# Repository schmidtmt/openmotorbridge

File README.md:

# OpenMotorBridge (v10.0) - Universal Motorcycle Intercom & Telemetry Bridge

<p align="center">
  
  &nbsp;&nbsp;&nbsp;&nbsp;&nbsp;&nbsp;&nbsp;&nbsp;
  
</p>

<p align="center">

</p>

**OpenMotorBridge (OMB)** is an open-source, cross-vendor communication and telemetry bridge for motorcycles. It seamlessly interconnects proprietary wireless intercom systems (**Sena Mesh 3.0** and **Cardo DMC Gen2**) with an open **2.4 GHz / 868 MHz OpenMotorMesh (OMM)**, high-precision **GNSS Tour Logging (Automotive Dead Reckoning)**, and a **wireless WebBLE PWA cockpit dashboard**.

---

## 📚 Technical Documentation

The comprehensive technical specification is split into 18 logically organized chapters:

1. [**01 - System Architecture & Satellite Topology**](docs/en/01_system_architecture.md)  
   *The 5 standardized functional nodes, de-sensing philosophy, RF diversity, whitepaper engineering decisions, and cockpit integration.*

2. [**02 - Intercom Matrix, Hardware Profiles & Routing**](docs/en/02_intercom_matrix_profiles.md)  
   *The 5 OEM adapter classes A-E, LittleFS profile engine, zero-latency PTT (< 1.8 ms), and audio cross-matrix.*

3. [**03 - Audio DSP, Acoustics & Knowles MEMS Wind Tracking**](docs/en/03_audio_dsp_acoustics.md)  
   *1500V Bourns isolation, ES8388 Codec, Knowles MEMS acoustic wind sampling, and Raised-Cosine Ducking.*

4. [**04 - Mesh Network, LoRa & GNSS Navigation**](docs/en/04_mesh_lora_navigation.md)  
   *OpenMotorMesh (OMM), Dynamic Leader Election (DLE), 868 MHz LoRa fallback, and 10 Hz Multi-GNSS.*

5. [**05 - Power Management, UPS Battery & Power Gate**](docs/en/05_power_management_ups.md)  
   *LM5164-Q1 72V buck, BQ24075 UPS, TPS4H160-Q1 Quad Smart Switch, Front Node TPS54302 / SW3526 30W PD & 1-click CarPlay hard reboot.*

6. [**06 - Telemetry Blackbox, SDIO Ringbuffer & WebDAV Sync**](docs/en/06_telemetry_blackbox_webdav.md)  
   *4-bit high-speed SDIO, GDPR/court-compliant ringbuffer, ECDSA SHA-256, and automated private cloud sync.*

7. [**07 - Hardware Architecture & Board Pinouts (All 10 PCBAs)**](docs/en/07_pcba_hardware_pinouts.md)  
   *All 10 active circuit boards: layer stackup, controlled impedance, net classes, functional zoning, and pinout tables (`PCBA 01`, `03`, `05`, `05B`, `05C`, `05D`, `07`, `08`, `09`, `10`).*

8. [**08 - Mechanical Enclosures, CAD & Reference Mounting Kits**](docs/en/08_enclosures_mechanics_cad.md)  
   *Screwless Dual-Rail Slide-In Monocoques (Type A & B), Under-Perch Mirror Pod (`PCBA 05C`), 5-Port Glovebox Hub (`PCBA 05B`), Sensor Puck (`PCBA 05D`), Radar 2.0 Winged Housing with Garmin Bayonet, and 4-pin IP67 magnetic breakaway couplers.*

9. [**09 - Firmware Architecture, FreeRTOS & Rollback-OTA**](docs/en/09_firmware_architecture.md)  
   *Multi-core ESP32-S31 (Main) & ESP32-S31 + ESP32-E22 (Front), Pod Co-Processors (ESP32-C6), ESP-NOW low-latency protocol (< 1.8 ms), and dual-bank rollback OTA.*

10. [**10 - WebApp PWA & Dashboard Operation**](docs/en/10_webapp_pwa_dashboard.md)  
    *Zero-cloud PWA web app, Web Bluetooth API (WebBLE), vehicle dynamics HUD, Front Node controls, Support-Van / Convoy profile modes, and 4-tier GPX export.*

11. [**11 - Smart-Managed CarPlay & Android Auto Bridge Architecture (PCBA 05)**](docs/en/11_carplay_android_auto_bridge_architecture.md)  
    *Harley Skyline OS / Boom! Box integration, CP2AA protocol bridge, Virtual WHIM bypass, source-gated handlebar controls & headless dongle management.*

12. [**12 - Vehicle CAN-Bus Profiles, DBC JSON Schema & Universal Telemetry Engine**](docs/en/12_can_bus_vehicle_profiles.md)  
    *Data-driven LittleFS profiles for Harley-Davidson, BMW Motorrad, KTM, and OBD2, passive listen-only protection, and EKF tunnel dead reckoning.*

13. [**13 - Digital Simulation & Multi-Physics Master Testbench**](docs/en/13_simulation_testbench.md)  
    *9 modular Python testbenches and 10 HIL scenarios verifying SPICE, thermal, transients, RF, and acoustics.*

14. [**14 - EMC Hardening, RF Shielding & Environmental Protection**](docs/en/14_emv_rf_hardening.md)  
    *Automotive transient immunity (ISO 7637-2), 2.4 GHz vs 868 MHz isolation, IPC-CC-830B coating, and shock damping.*

15. [**15 - Bill of Materials (BOM) & SMT Manufacturing (All 10 PCBAs)**](docs/en/15_bom_manufacturing.md)  
    *Complete 10-board BOM for JLCPCB SMT production, ordering checklist, two-cable backbone harness, and COTS items.*

16. [**16 - Build Instructions, Wiring & Vehicle Installation**](docs/en/16_build_instructions_assembly.md)  
    *Step-by-step assembly guide for screwless v10 Slide-In Monocoques, 3D printing parameters (FDM vs. MJF), Front Node & Glovebox Hub mounting, Harley 4-pin magnetic side-wall pass-through, Smart-Keyfob build, and commissioning.*

17. [**17 - Automotive Standards & Technical References**](docs/en/17_standards_references.md)  
    *Index for ISO 7637-2, ISO 16750, ECE R10, RED 2014/53/EU, IEC 61672-1 Class 1, and Bluetooth SIG.*

18. [**18 - Legal Compliance, Privacy (GDPR) & Licensing**](docs/en/18_legal_compliance_dsgvo.md)  
    *Open-source licenses (GPL-3.0, CERN-OHL-S v2, CC BY-SA 4.0), GDPR compliance, and liability disclaimer.*

---

## 🛠️ Repository Layout

* **`docs/de/`**: Complete technical specifications in German.
* **`docs/en/`**: Complete technical specifications in English.
* **`firmware/main_controller/`**: ESP-IDF / C++ source code for the central main box (ESP32-S31, PCBA 01).
* **`firmware/front_node/`**: ESP-IDF / C++ source code for the Universal Front Node (ESP32-S31 + ESP32-E22, PCBA 05).
* **`firmware/smart_cartridge/`**: ESP-IDF / C++ source code for Saddlebag Pod Gateways Pod 1 & 2 (ESP32-C6, PCBA 03).
* **`firmware/radar_submcu/`**: ESP-IDF / C++ source code for Heck-Radar 2.0 Sub-MCU & Halo Wings (ESP32-C5, PCBA 08).
* **`webapp_pwa/`**: Zero-cloud offline WebBLE dashboard (HTML5, Vanilla JS, CSS3, Service Worker, i18n).
* **`hardware/`**: KiCad schematics, Gerber files, and 3D enclosure CAD models.
* **`tools/audio_testbench/`**: **Interactive Live Audio DSP Studio & Real-Time Testbench** (`python3 tools/audio_testbench/server.py` $\rightarrow$ Web Audio testbench with live mic, Spacebar PTT, speedometer & ducking).
* **`tools/simulators/`**: 9 modular Python simulation testbenches (`python3 tools/run_all_simulations.py`).

---

## 📜 Licenses

* **Hardware & PCB Layouts:** [CERN-OHL-S v2](https://ohwr.org/project/cernohl/wikis/Documents/CERN-OHL-version-2) (Strongly Reciprocal)
* **Firmware & Web Dashboard:** [GNU General Public License v3.0 (GPL-3.0)](https://www.gnu.org/licenses/gpl-3.0.html)
* **Documentation & 3D Models:** [Creative Commons Attribution-ShareAlike 4.0 International (CC BY-SA 4.0)](https://creativecommons.org/licenses/by-sa/4.0/)

---

## ⚠️ Liability Disclaimer

All information, schematics, board layouts, 3D printing files, and software published in this project are provided free of charge on an "AS IS" basis. Assembly, installation, and operation occur entirely at the user's own risk. All mentioned brand names (Harley-Davidson®, BMW®, Garmin®, Sena®, Cardo®, Apple CarPlay®) are registered trademarks of their respective owners.

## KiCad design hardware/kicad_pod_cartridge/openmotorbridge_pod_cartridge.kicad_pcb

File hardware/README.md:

# OpenMotorBridge v8.5 / v9.0 - KiCad Hardware-Baukasten (Clean All-UWB Architecture)

Dieses Verzeichnis enthält die vollständigen **KiCad 10 Schaltplan-, PCB- und Produktionsdateien** für die drahtlose **All-UWB & Pure-DC Architektur** von OpenMotorBridge.

---

## 📂 Das bereinigte 6-Platinen-Lineup

Durch den konsequenten Einsatz von Ultra-Wideband (Qorvo DW3110 6.5 GHz Ch. 5, $< 0{,}4\,\text{ms}$) und Bluetooth entfällt jegliche Signal- und NF-Audioverdrahtung über den Rahmen. Der Kabelbaum besteht ausschließlich aus robusten **2-Draht-DC-Power-Peitschen** (+5V/GND bzw. +12V/GND). 

Die Pod-Platine (`PCBA 02`) und der Heck-Pod (`PCBA 04`) sind ersatzlos entfallen - der Baukasten besteht aus **exakt 6 aktiven PCBAs**:

| PCBA | Baugruppe & Funktion | Maße / Lagen | Kern-Komponenten / RF |
| :--- | :--- | :--- | :--- |
| **PCBA 01** | **Zentralbox Main Controller**<br>*(Unter Sitzbank, Audio-DSP, USV)* | 85 x 55 mm<br>4 Lagen (ENIG) | ESP32-S3, ES8388 24-Bit Codec, TCAN334G CAN-FD, LM5164-Q1, SX1262 LoRa (Top), DW3110 UWB (Bottom), SW1 Taster |
| **PCBA 03** | **Universal Smart Cartridge Rev 3.0**<br>*(Autarker UWB-Funkschlitten)* | 35 x 25 mm<br>2 Lagen (ENIG, 2-seitig SMT) | Qorvo DW3110 UWB, SPI Host-MCU, 4x AO3400A MOSFETs, 2P Frontkontakt (+5V/GND), DNP-Codec |
| **PCBA 05** | **Universal Front-Knoten**<br>*(Cockpit Hub, Sensorik, Audio, USB-PD)* | 82 x 50 mm<br>4 Lagen (ENIG) | ESP32-S3, DW3110 UWB, SAM-M10Q, USB2514B Hub, Dual SW3526 PD20W, Qi 12V, BSD LEDs |
| **PCBA 06** | **MagSafe Frame Dock Adapter**<br>*(Rahmendock M8 auf 2-Pin MagSafe)* | 28 x 11.5 mm<br>2 Lagen (1 oz) | 2 Pogo-Pins (+5V / GND), TVS Diode, 16V PPTC Polyfuse |
| **PCBA 07** | **2-in-1 LoRa Smart-Keyfob & Pager**<br>*(Taschen-Pager, N52 Key & Qi)* | 38 x 19 mm<br>2 Lagen (ENIG) | Nordic nRF52840 SoC, Semtech SX1262 LoRa, DRV2605L Haptik, BQ51003 Qi RX |
| **PCBA 08** | **Radar 2.0 Sub-MCU & Wings**<br>*(Wheeltec 77GHz MR20 + Halo LED)* | 115 x 65 mm<br>2 Lagen (ENIG) | ESP32 Sub-MCU (UWB DW3110), 36x WS2812B LEDs, 2-Pin 12V Power |

---

## 🔌 Zentraler Bordnetz-Stecker (Deutsch DTM-12 Automotive)

Die Zentralbox nutzt einen robusten, wasserdichten **Deutsch DTM-12 Industriestecker** (11 aktive Kontakte):

| Pin | Signalname | Funktion | Querschnitt / Ziel |
| :---: | :--- | :--- | :--- |
| **1** | `KL30_IN` | 12V Dauerplus | AWG20 (0.50 mm²) / Bordnetz |
| **2** | `KL15_IGN` | 12V Zündungsplus | AWG22 (0.34 mm²) / Zündung |
| **3** | `VEHICLE_GND`| Hauptmasse (KL31) | AWG20 (0.50 mm²) / Rahmen |
| **4** | `CAN_H` | Fahrzeug-CAN High | AWG24 (0.22 mm²) / Twisted Pair |
| **5** | `CAN_L` | Fahrzeug-CAN Low | AWG24 (0.22 mm²) / Twisted Pair |
| **6** | `POD1_VCC` | 5V Switched Power Bucht 1 (Links) | AWG22 (0.34 mm²) / JWPF 2P |
| **7** | `POD1_GND` | Masse Bucht 1 (Links) | AWG22 (0.34 mm²) / JWPF 2P |
| **8** | `POD2_VCC` | 5V Switched Power Bucht 2 (Rechts) | AWG22 (0.34 mm²) / JWPF 2P |
| **9** | `POD2_GND` | Masse Bucht 2 (Rechts) | AWG22 (0.34 mm²) / JWPF 2P |
| **10**| `RADAR_PWR` | 12V Switched Power Radar Heck | AWG22 (0.34 mm²) / JWPF 2P |
| **11**| `RADAR_GND` | Masse Radar | AWG22 (0.34 mm²) / JWPF 2P |
| **12**| `CHASSIS_EARTH` | Gehäuseschirm / Rahmenerde | AWG20 (0.50 mm²) |

---

## 🛠️ Fertigung & Validierung (JLCPCB / Eurocircuits)

* **Produktionspakete generieren:**
  ```bash
  python3 hardware/scripts/export_manufacturing_packages.py
  ```
* **JLCPCB DFM & Netlist-Verifikation:**
  ```bash
  /Applications/KiCad/KiCad.app/Contents/Frameworks/Python.framework/Versions/3.9/bin/python3 hardware/scripts/verify_pcb_designs_jlcpcb.py
  ```

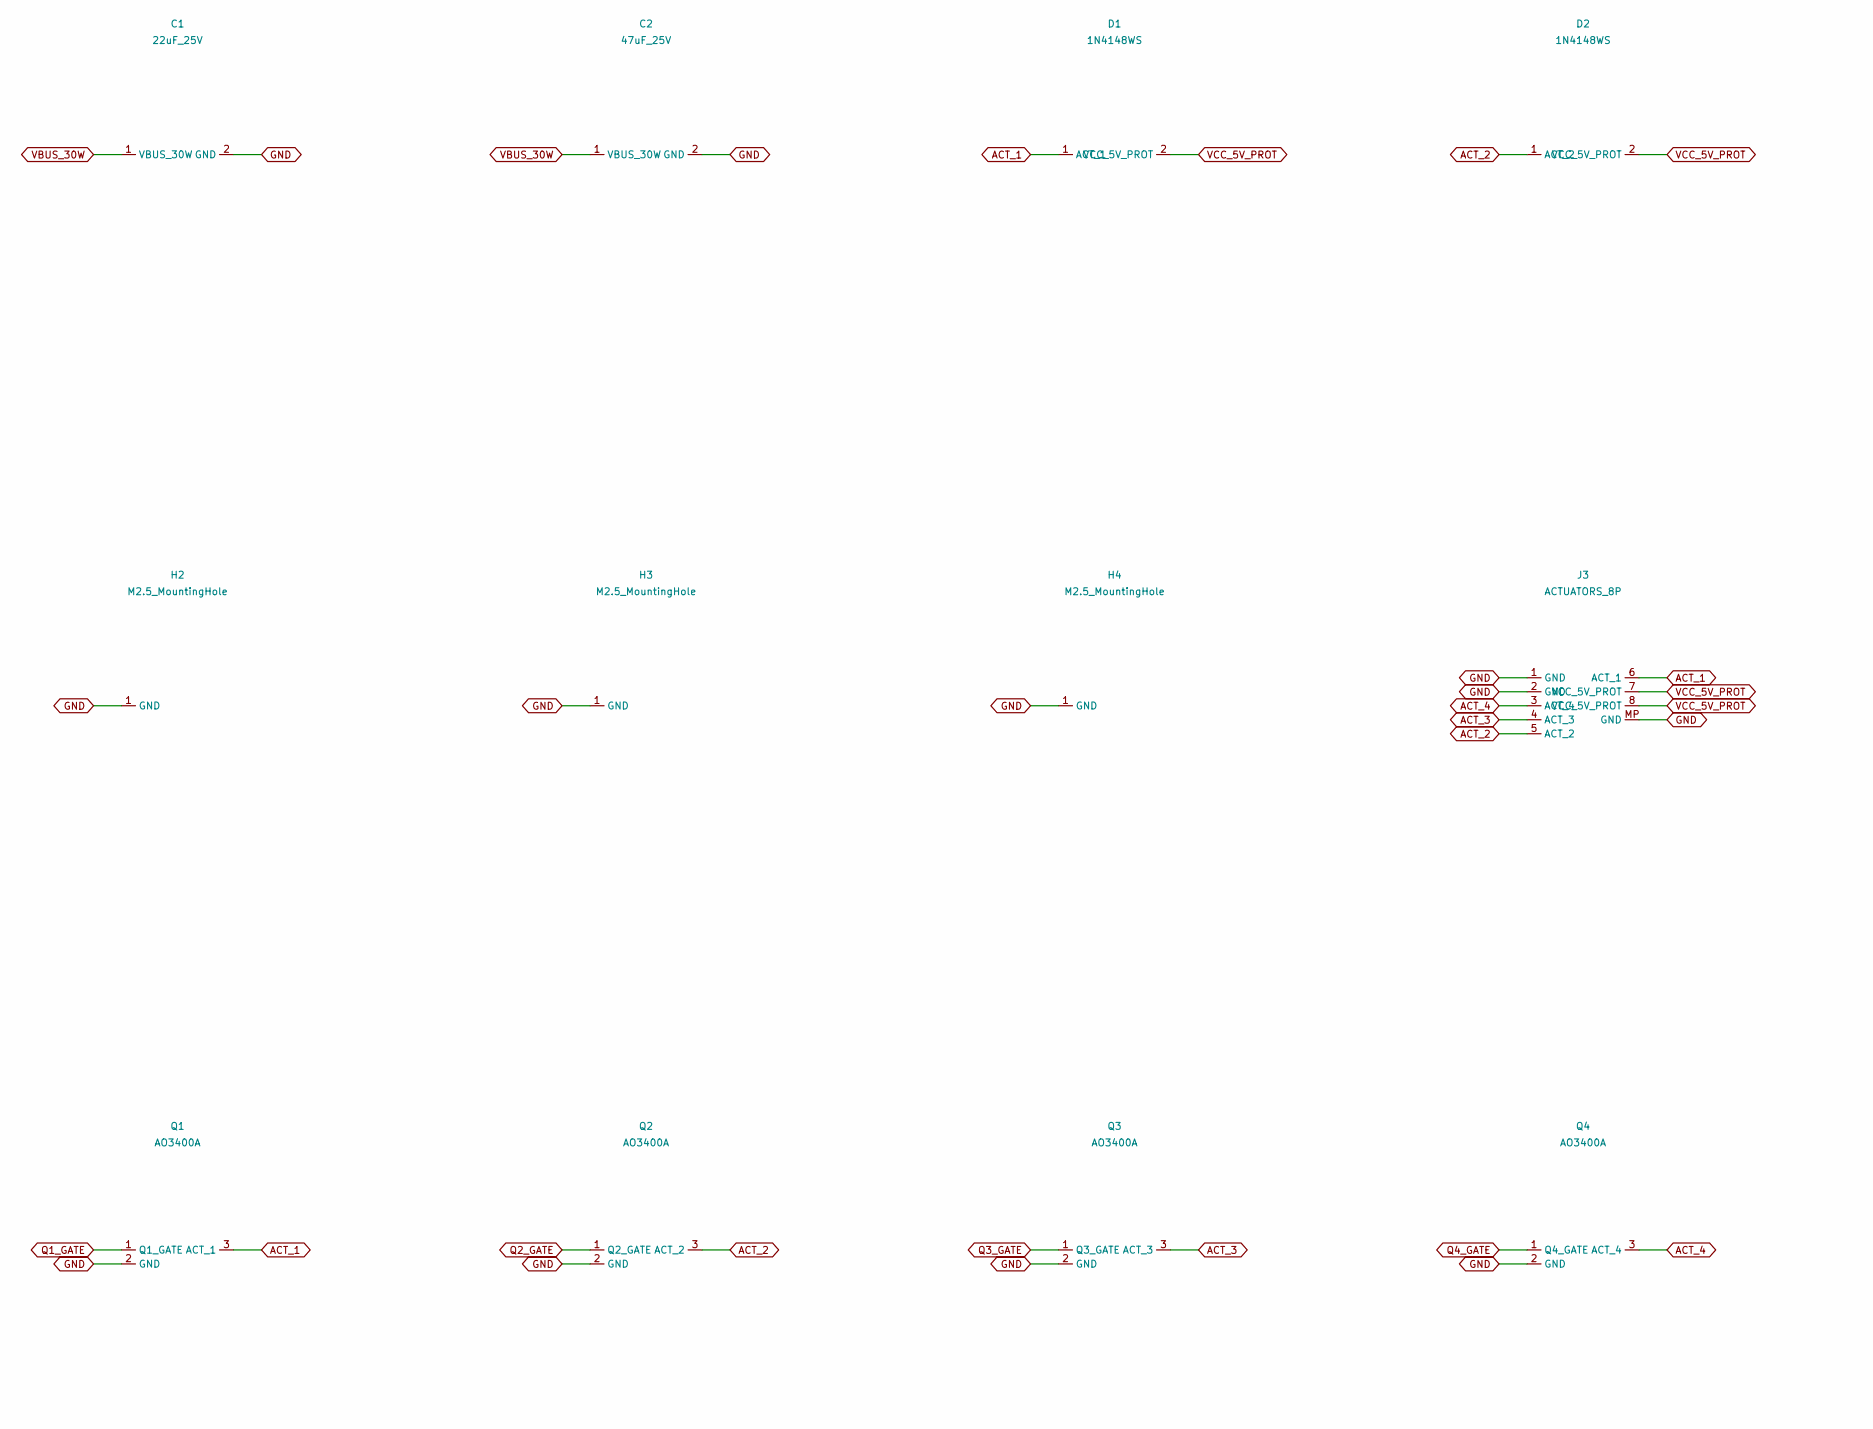
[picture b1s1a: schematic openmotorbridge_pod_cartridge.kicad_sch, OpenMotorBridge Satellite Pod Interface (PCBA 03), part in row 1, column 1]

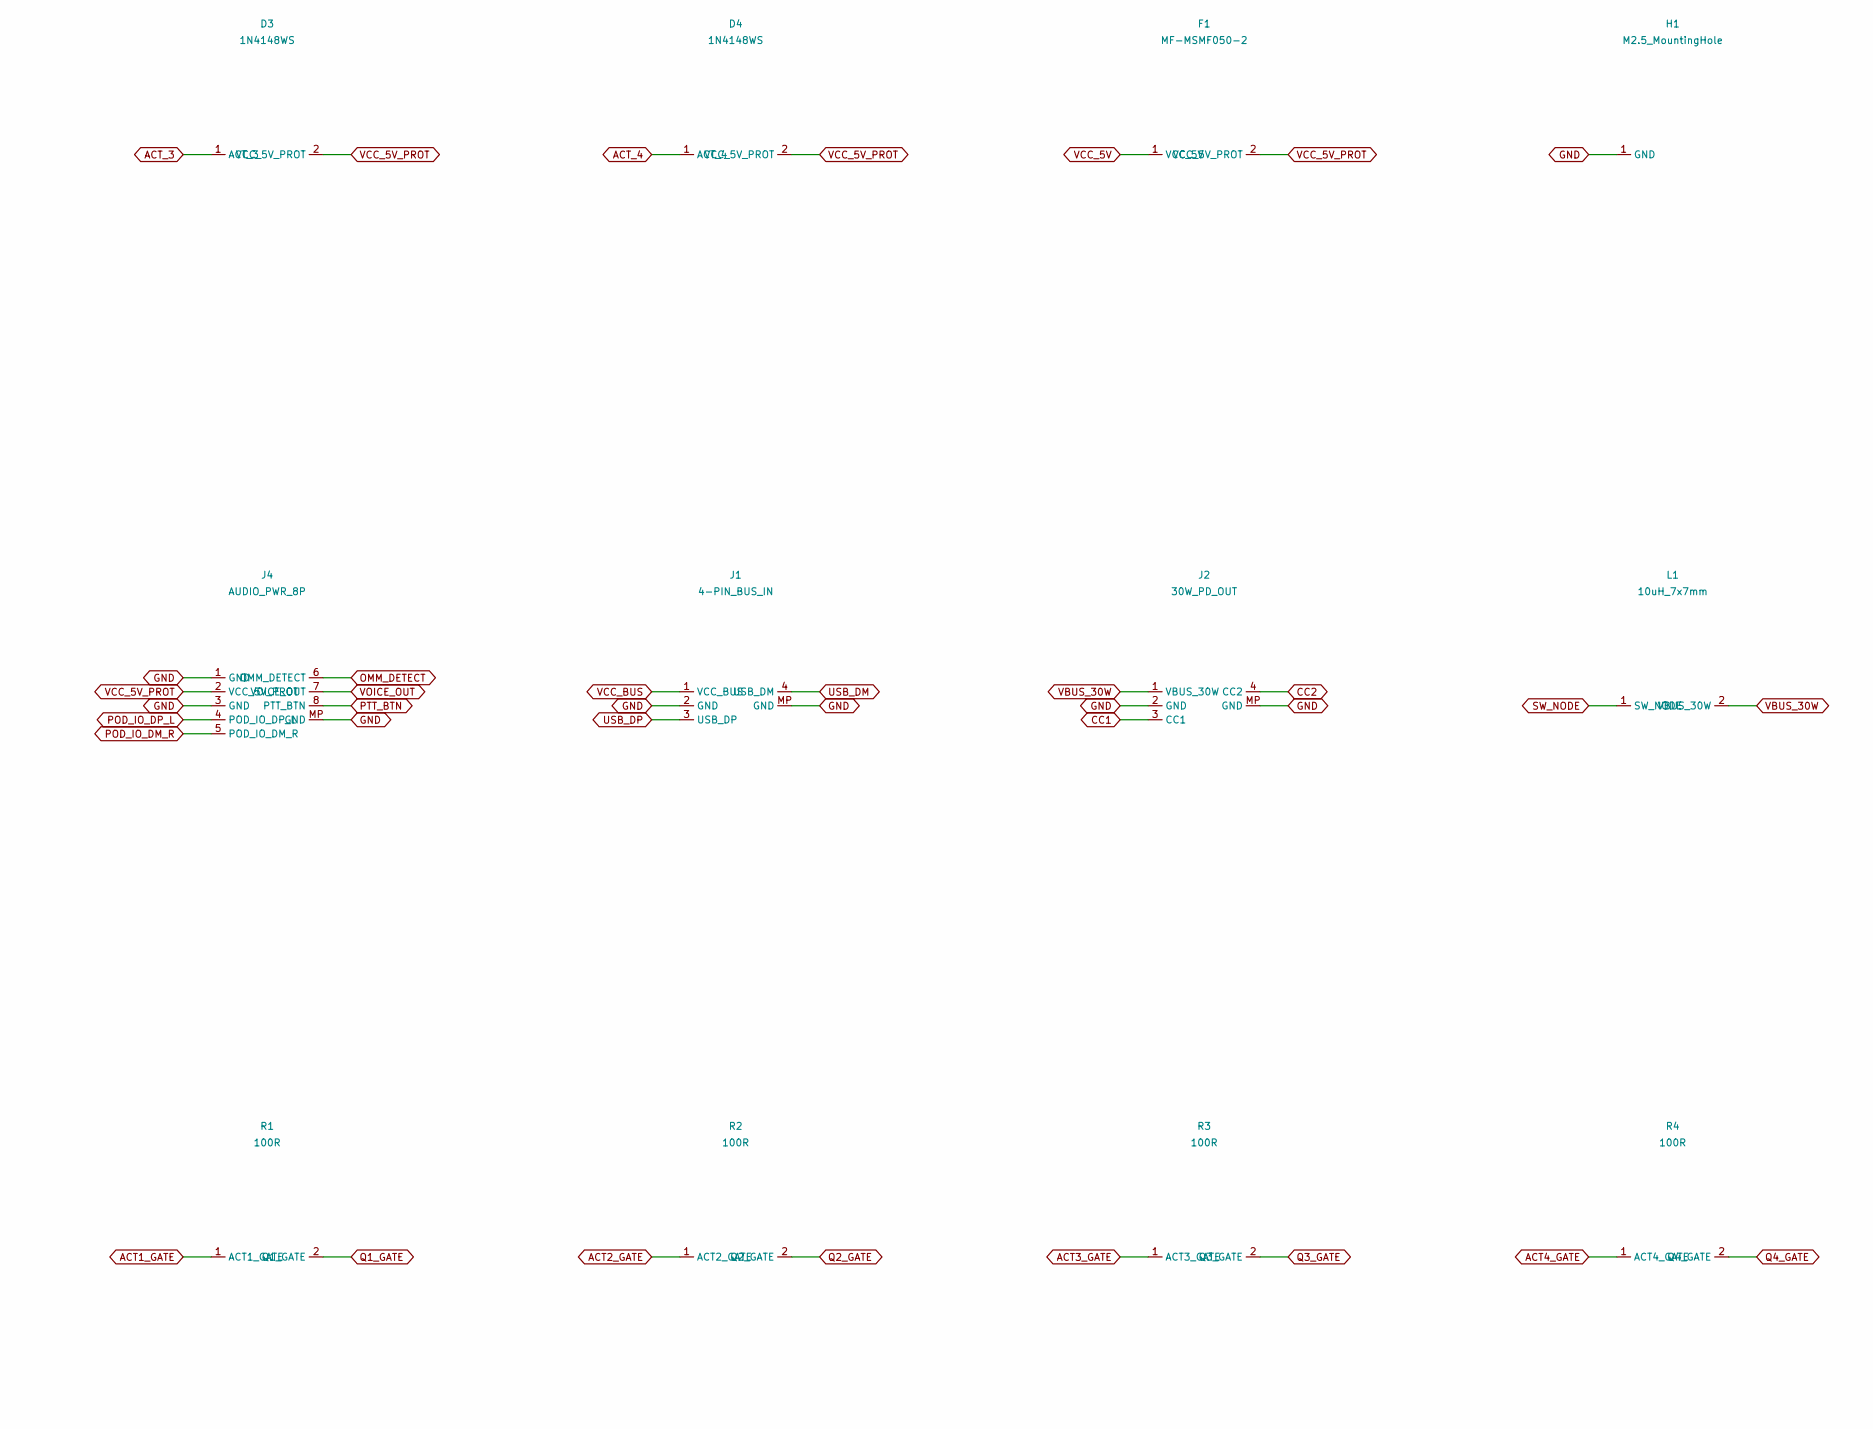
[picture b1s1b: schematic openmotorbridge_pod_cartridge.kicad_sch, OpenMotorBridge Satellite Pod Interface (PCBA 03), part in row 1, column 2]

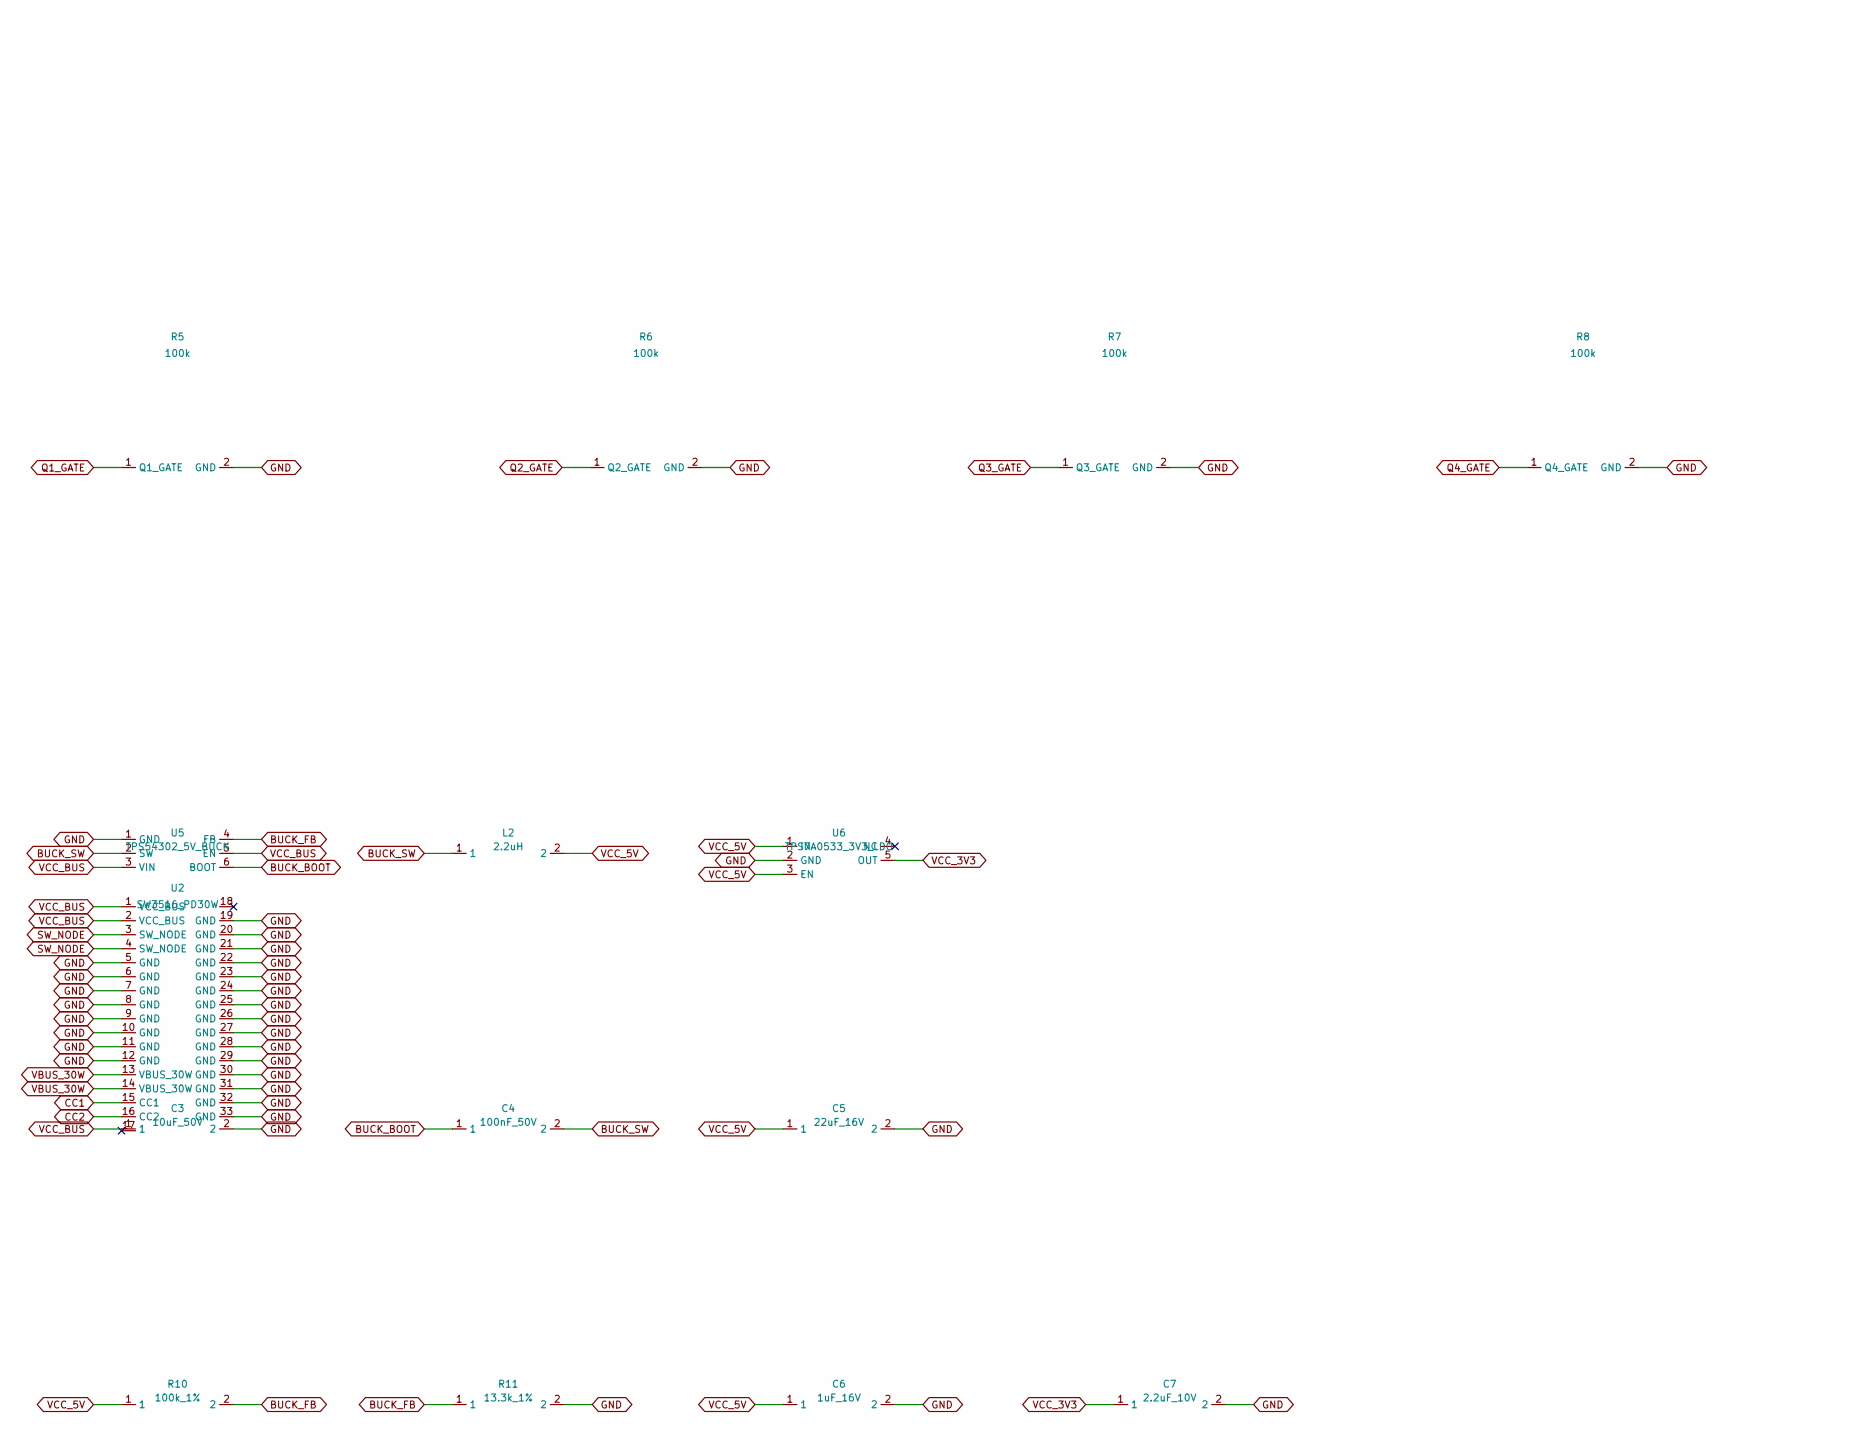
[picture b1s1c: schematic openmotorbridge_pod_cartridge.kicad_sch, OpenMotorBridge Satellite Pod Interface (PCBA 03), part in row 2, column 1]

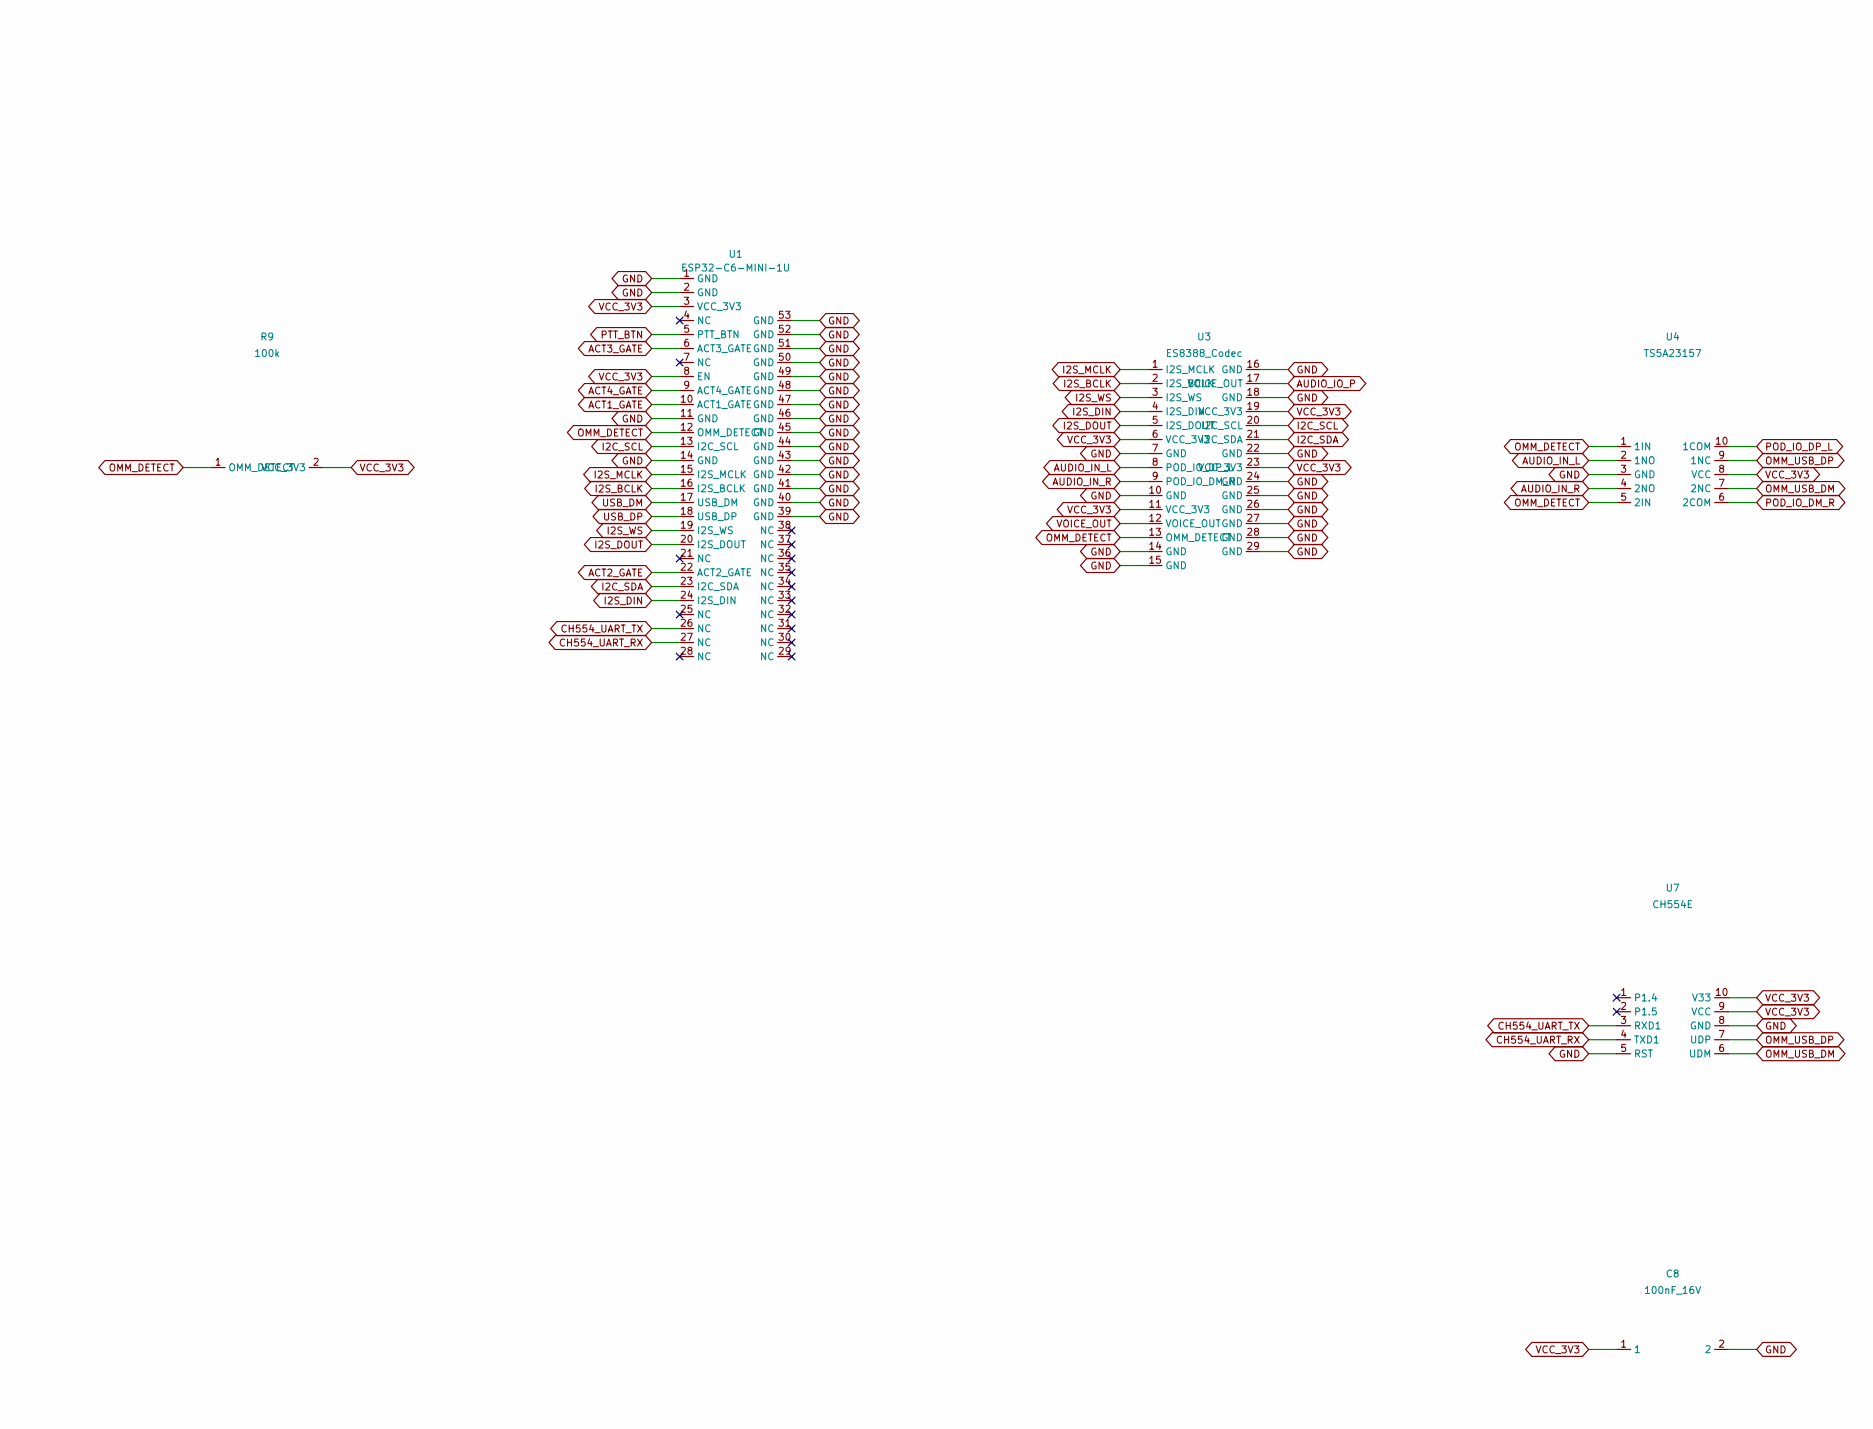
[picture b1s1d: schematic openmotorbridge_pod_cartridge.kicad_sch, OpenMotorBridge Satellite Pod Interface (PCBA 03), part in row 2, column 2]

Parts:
C1: 22uF_25V; C_1210_3225Metric
C2: 47uF_25V; C_1210_3225Metric
C3: 10uF_50V; C_0805_2012Metric
C4: 100nF_50V; C_0603_1608Metric
C5: 22uF_16V; C_0805_2012Metric
C6: 1uF_16V; C_0603_1608Metric
C7: 2.2uF_10V; C_0603_1608Metric
C8: 100nF_16V; C_0603_1608Metric
D1, D2, D3, D4: 1N4148WS; D_SOD-323
F1: MF-MSMF050-2; Fuse_1812_4532Metric
H1, H2, H3, H4: M2.5_MountingHole; MountingHole_2.7mm_M2.5_Pad
J1: 4-PIN_BUS_IN; JST_GH_BM04B-GHS-TBT_1x04-1MP_P1.25mm_Vertical
J2: 30W_PD_OUT; JST_GH_BM04B-GHS-TBT_1x04-1MP_P1.25mm_Vertical
J3: ACTUATORS_8P; JST_SH_BM08B-SRSS-TB_1x08-1MP_P1.00mm_Vertical
J4: AUDIO_PWR_8P; JST_SH_BM08B-SRSS-TB_1x08-1MP_P1.00mm_Vertical
L1: 10uH_7x7mm; L_Wuerth_WE-PD-Typ-7345
L2: 2.2uH; L_0805_2012Metric
Q1, Q2, Q3, Q4: AO3400A; SOT-23
R1, R2, R3, R4: 100R; R_0603_1608Metric
R5, R6, R7, R8, R9: 100k; R_0603_1608Metric
R10: 100k_1%; R_0603_1608Metric
R11: 13.3k_1%; R_0603_1608Metric
U1: ESP32-C6-MINI-1U
U2: SW3516_PD30W; QFN-32-1EP_5x5mm_P0.5mm_EP3.45x3.45mm_ThermalVias
U3: ES8388_Codec; QFN-28-1EP_4x4mm_P0.4mm_EP2.4x2.4mm
U4: TS5A23157; MSOP-10_3x3mm_P0.5mm
U5: TPS54302_5V_BUCK; SOT-23-6
U6: TPS7A0533_3V3_LDO; SOT-23-5
U7: CH554E; MSOP-10_3x3mm_P0.5mm

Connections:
ACT1_GATE: R1.1 (ACT1_GATE), U1.10 (ACT1_GATE)
ACT2_GATE: R2.1 (ACT2_GATE), U1.22 (ACT2_GATE)
ACT3_GATE: R3.1 (ACT3_GATE), U1.6 (ACT3_GATE)
ACT4_GATE: R4.1 (ACT4_GATE), U1.9 (ACT4_GATE)
ACT_1: D1.1 (ACT_1), J3.6 (ACT_1), Q1.3 (ACT_1)
ACT_2: D2.1 (ACT_2), J3.5 (ACT_2), Q2.3 (ACT_2)
ACT_3: D3.1 (ACT_3), J3.4 (ACT_3), Q3.3 (ACT_3)
ACT_4: D4.1 (ACT_4), J3.3 (ACT_4), Q4.3 (ACT_4)
AUDIO_IN_L: U3.8 (AUDIO_IN_L), U4.2 (1NO)
AUDIO_IN_R: U3.9 (AUDIO_IN_R), U4.4 (2NO)
AUDIO_IO_P: U3.17 (AUDIO_IO_P)
BUCK_BOOT: C4.1, U5.6 (BOOT)
BUCK_FB: R10.2, R11.1, U5.4 (FB)
BUCK_SW: C4.2, L2.1, U5.2 (SW)
CC1: J2.3 (CC1), U2.15 (CC1)
CC2: J2.4 (CC2), U2.16 (CC2)
CH554_UART_RX: U1.27 (NC), U7.4 (TXD1)
CH554_UART_TX: U1.26 (NC), U7.3 (RXD1)
GND: C1.2 (GND), C2.2 (GND), C3.2, C5.2, C6.2, C7.2, C8.2, H1.1 (GND_1), H2.1 (GND_1), H3.1 (GND_1), H4.1 (GND_1), J1.2 (GND), J1.MP (GND), J2.2 (GND), J2.MP (GND), J3.1 (GND), J3.2 (GND), J3.MP (GND), J4.1 (GND), J4.3 (GND), J4.MP (GND), Q1.2 (GND), Q2.2 (GND), Q3.2 (GND), Q4.2 (GND), R5.2 (GND), R6.2 (GND), R7.2 (GND), R8.2 (GND), R11.2, U1.1 (GND), U1.2 (GND), U1.11 (GND), U1.14 (GND), U1.39 (GND), U1.40 (GND), U1.41 (GND), U1.42 (GND), U1.43 (GND), U1.44 (GND), U1.45 (GND), U1.46 (GND), U1.47 (GND), U1.48 (GND), U1.49 (GND), U1.50 (GND), U1.51 (GND), U1.52 (GND), U1.53 (GND), U2.5 (GND), U2.6 (GND), U2.7 (GND), U2.8 (GND), U2.9 (GND), U2.10 (GND), U2.11 (GND), U2.12 (GND), U2.19 (GND), U2.20 (GND), U2.21 (GND), U2.22 (GND), U2.23 (GND), U2.24 (GND), U2.25 (GND), U2.26 (GND), U2.27 (GND), U2.28 (GND), U2.29 (GND), U2.30 (GND), U2.31 (GND), U2.32 (GND), U2.33 (GND), U3.7 (GND), U3.10 (GND), U3.14 (GND), U3.15 (GND), U3.16 (GND), U3.18 (GND), U3.22 (GND), U3.24 (GND), U3.25 (GND), U3.26 (GND), U3.27 (GND), U3.28 (GND), U3.29 (GND), U4.3 (GND), U5.1 (GND), U6.2 (GND), U7.5 (RST), U7.8 (GND)
I2C_SCL: U1.13 (I2C_SCL), U3.20 (I2C_SCL)
I2C_SDA: U1.23 (I2C_SDA), U3.21 (I2C_SDA)
I2S_BCLK: U1.16 (I2S_BCLK), U3.2 (I2S_BCLK)
I2S_DIN: U1.24 (I2S_DIN), U3.4 (I2S_DIN)
I2S_DOUT: U1.20 (I2S_DOUT), U3.5 (I2S_DOUT)
I2S_MCLK: U1.15 (I2S_MCLK), U3.1 (I2S_MCLK)
I2S_WS: U1.19 (I2S_WS), U3.3 (I2S_WS)
OMM_DETECT: J4.6 (OMM_DETECT), R9.1 (OMM_DETECT), U1.12 (OMM_DETECT), U3.13 (OMM_DETECT), U4.1 (1IN), U4.5 (2IN)
OMM_USB_DM: U4.7 (2NC), U7.6 (UDM)
OMM_USB_DP: U4.9 (1NC), U7.7 (UDP)
POD_IO_DM_R: J4.5 (AUDIO_IN_R), U4.6 (2COM)
POD_IO_DP_L: J4.4 (AUDIO_IN_L), U4.10 (1COM)
PTT_BTN: J4.8 (PTT_BTN), U1.5 (PTT_BTN)
Q1_GATE: Q1.1 (Q1_GATE), R1.2 (Q1_GATE), R5.1 (Q1_GATE)
Q2_GATE: Q2.1 (Q2_GATE), R2.2 (Q2_GATE), R6.1 (Q2_GATE)
Q3_GATE: Q3.1 (Q3_GATE), R3.2 (Q3_GATE), R7.1 (Q3_GATE)
Q4_GATE: Q4.1 (Q4_GATE), R4.2 (Q4_GATE), R8.1 (Q4_GATE)
SW_NODE: L1.1 (SW_NODE), U2.3 (SW_NODE), U2.4 (SW_NODE)
USB_DM: J1.4 (USB_DM), U1.17 (USB_DM)
USB_DP: J1.3 (USB_DP), U1.18 (USB_DP)
VBUS_30W: C1.1 (VBUS_30W), C2.1 (VBUS_30W), J2.1 (VBUS_30W), L1.2 (VBUS_30W), U2.13 (VBUS_30W), U2.14 (VBUS_30W)
VCC_3V3: C7.1, C8.1, R9.2 (VCC_3V3), U1.3 (VCC_3V3), U1.8 (EN), U3.6 (VCC_3V3), U3.11 (VCC_3V3), U3.19 (VCC_3V3), U3.23 (VCC_3V3), U4.8 (VCC), U6.5 (OUT), U7.9 (VCC), U7.10 (V33)
VCC_5V: C5.1, C6.1, F1.1 (VCC_5V), L2.2, R10.1, U6.1 (IN), U6.3 (EN)
VCC_5V_PROT: D1.2 (VCC_5V_PROT), D2.2 (VCC_5V_PROT), D3.2 (VCC_5V_PROT), D4.2 (VCC_5V_PROT), F1.2 (VCC_5V_PROT), J3.7 (VCC_5V_PROT), J3.8 (VCC_5V_PROT), J4.2 (VCC_5V_PROT)
VCC_BUS: C3.1, J1.1 (VCC_BUS), U2.1 (VCC_BUS), U2.2 (VCC_BUS), U5.3 (VIN), U5.5 (EN)
VOICE_OUT: J4.7 (AUDIO_IO_P), U3.12 (VOICE_OUT)

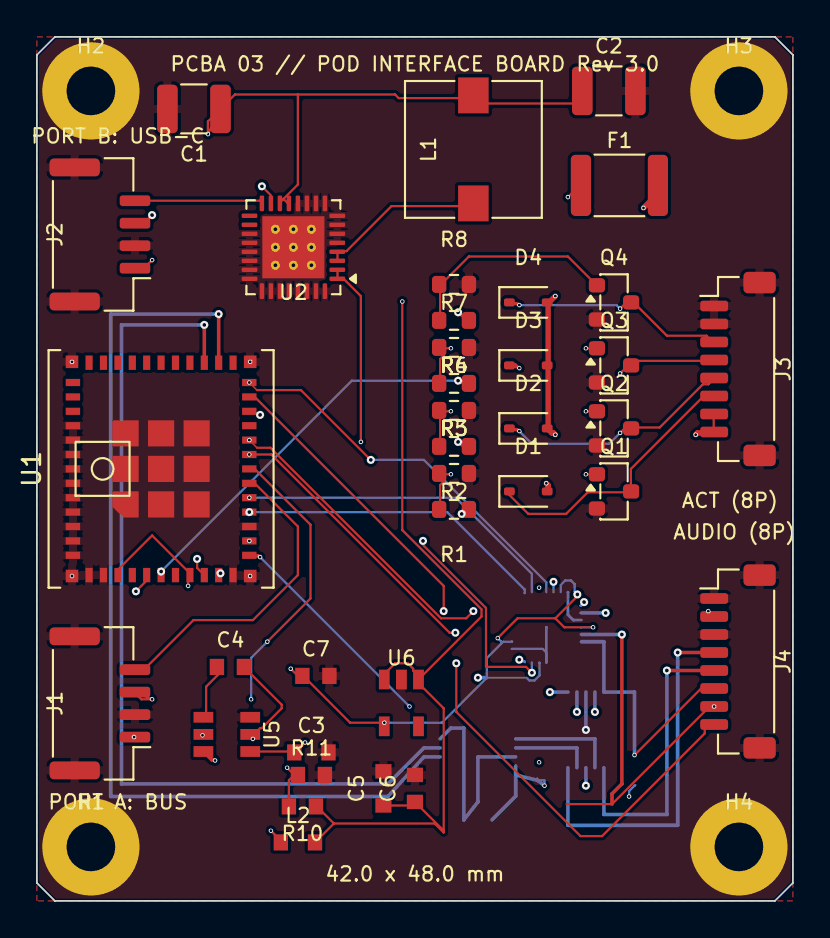
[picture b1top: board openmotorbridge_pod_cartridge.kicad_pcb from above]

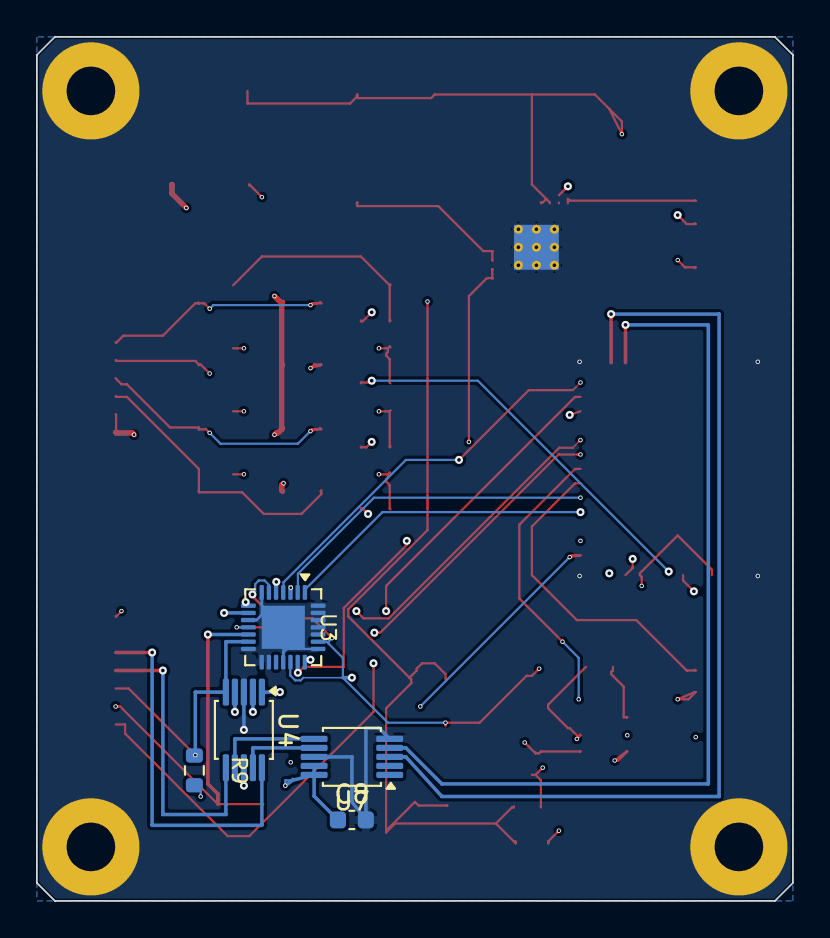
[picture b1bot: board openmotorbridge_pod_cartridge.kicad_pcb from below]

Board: 4 copper layers, 42.0 x 48.0 mm, 45 parts (5 on the bottom side), 44 nets.

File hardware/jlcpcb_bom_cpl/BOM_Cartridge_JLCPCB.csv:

Designator,Comment,Footprint,LCSC Part #,Quantity
C1,100nF,Capacitor_SMD:C_0603_1608Metric,,1
C2,10uF,Capacitor_SMD:C_0805_2012Metric,,1
"D1, D2, D3, D4",1N4148WS,Diode_SMD:D_SOD-323,,4
F1,MF-MSMF050-2,Fuse:Fuse_1812_4532Metric,,1
"H1, H2, H3, H4",M2_MountingHole,MountingHole:MountingHole_2.2mm_M2_Pad,,4
J1,POD_BASE_DOCKING_SOCKET_6P,Connector_PinSocket_2.54mm:PinSocket_1x06_P2.54mm_Horizontal,,1
J2,INTERCOM_HEADSET_6P,Connector_JST:JST_SH_SM06B-SRSS-TB_1x06-1MP_P1.00mm_Horizontal,,1
J_ACT,ACTUATORS_8P,Connector_JST:JST_SH_SM08B-SRSS-TB_1x08-1MP_P1.00mm_Horizontal,,1
"Q1, Q2, Q3, Q4",AO3400A,Package_TO_SOT_SMD:SOT-23,,4
"R1, R2, R3, R4",100R,Resistor_SMD:R_0603_1608Metric,,4
"R5, R6, R7, R8",100k,Resistor_SMD:R_0603_1608Metric,,4
R9,4.7k,Resistor_SMD:R_0603_1608Metric,,1
U1,CH32V003F4P6,Package_SO:TSSOP-20_4.4x6.5mm_P0.65mm,,1

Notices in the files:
README.md:
Hardware License: CERN-OHL-S v2
Software License: GPL v3
Documentation: CC BY-SA 4.0
